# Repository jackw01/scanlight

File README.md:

# A Better Light Source For Scanning Color Negative Film

Left: [scanlight v4](./v4.md), right: [big scanlight](./big.md)

<small>Originally published 2024-08-05, last updated 2026-08-02</small>

## tl;dr

Narrowband trichromatic (RGB) light sources are superior to broadband (white) light for scanning color negative film; there are very good reasons why all commercial film scanners use RGB. ([film scanners were using blue LEDs at least a decade before they would be widely used in consumer products!](https://patents.google.com/patent/JPH09130546A/en?q=(film+scanner+LED)&oq=film+scanner+LED&sort=old)) Scanning film with an RGB light source produces high quality results with minimal post-processing, without the need for specialized software.

### the results

<small>Both scans captured using Fujifilm X-T30. White light scan captured using 95+ CRI 5000K light source. RGB scan captured using custom 450nm+525nm+665nm light source.</small>

## the simplified explanation

Color negative (C-41) film stores an image using cyan, magenta, and yellow dyes. Dyes appear a certain color because they absorb some wavelengths of light; for example, yellow dye mostly absorbs light in the 400-550nm range (which we perceive as violet through green), while allowing other wavelengths (yellow through red) to pass through the film. **These dyes are not intended to produce a human-viewable image, but rather to attenuate certain wavelengths of light for making prints on photosensitive paper.**

White light sources emit light over a broad spectrum of wavelengths. When white light passes through C-41 film, some of these wavelengths are only slightly absorbed by the dyes, which means that these wavelengths aren't useful for recovering the information stored in the individual dye layers - for example, the 580-620nm band (yellow through red-orange light) is mostly transmitted through the film, with a small amount being absorbed by both the magenta and cyan dye layers.

The quality of white light sources is measured with CRI, which represents how well a light source reproduces the true color of a set of standardized color swatches. CRI is effectively a weighted average of how much light a light source emits across different parts of the visible light spectrum, and only a few of these parts matter when it comes to extracting information from color film. **CRI doesn't take into account the deep red (>630nm) and deep blue (<480nm) parts of the spectrum, so as a result, many high-CRI LEDs don't emit much light at these wavelengths, which happen to be where the yellow and cyan dyes absorb the most light.**

<small>note: Standardized scores that take into account these wavelength bands at the edges of the visible spectrum do exist (R9 and R12), but are not readily provided by all LED manufacturers.</small>

With darkroom printing, this is not an issue, as RA-4 color print paper (and motion picture print film) are, by design, most sensitive to specific bands of wavelengths that avoid the crosstalk regions between the dye layers in negative film, and the paper is exposed with an incandescent light source with a smooth emission spectrum across the entire visible range (400-700nm) and beyond.

What about scanning film with a digital camera? Digital camera sensors are designed to capture light in a way that allows for a faithful reproduction of the colors that humans would perceive (this is a gross oversimplification.) C-41 film was *not* designed to be directly viewed by humans.

Not only is the camera sensitive to wavelengths of light that are effectively ignored by RA-4 paper, there is significant crosstalk between the color channel sensitivities of digital camera sensors: light in the ~580-600nm range is seen roughly equally by the red and green channels, and light in the ~480-500nm range is seen by both the green and blue channels.

The red channel of the scan will contain not just information from the red-blocking cyan dye, but also the green-blocking magenta dye. The green channel will contain information from all three dye layers. Additionally, the overall light transmission of C-41 film is heavily biased towards yellow and orange wavelengths due to the orange mask and the relatively large gap between the magenta and cyan dye absorption peaks, which means that **a lot** of light gets through that interferes with both the red and green channels in the camera sensor without carrying much useful information about the colors stored in the film.

<small>note: the orange color of C-41 film is often misunderstood to be the color of the plastic film base, or an orange tint evenly applied over the whole image. It is actually a corrective mask made up of blue- and green-blocking positive images which compensate for deficiencies in the red-sensing and green-sensing layers of the film. For a good explanation of how this works, see [this article](https://observablehq.com/@dorskyee/understanding-color-film). In practice, this means that less-exposed parts of the negative let through disproportionately more yellow, orange, and red light.</small>

So if you scan color negative film with white light, you can't just invert the colors and expect a good result. You need to do some math to try to recover the individual dye layers of the film from ambiguous input data. This can't be done in standard image editing software, which is why dedicated software for negative conversion exists. The level of crosstalk on each channel depends heavily on both the emission spectra of the light source and the spectral sensitivity of the camera, so the conversion process needs to be either calibrated, manually adjusted until it looks “right”, or deduced by the processing software with varying degrees of accuracy. The color depth of the resulting positive image will be relatively low because much of the information recorded by the camera is effectively useless yellow-orange light that has passed through the film without being significantly attenuated by any of the dyes.

To avoid these issues, (almost?) all commercial negative film scanners use a trichromatic narrowband light source with red, green, and blue LEDs to minimize crosstalk between the dye layers in the film and the color channels on the image sensor, and some use monochrome sensors to eliminate sensor crosstalk entirely. When doing it this way, no guesswork is needed to recover a usable image and it's really as simple as inverting the color channels and setting the color balance and black/white points. There is still some crosstalk between camera sensor channels, but now that the light source emits light in three narrow, independently controllable wavelength bands, it can be easily measured and compensated for, or it can be avoided completely by imaging the red, green, and blue channels separately.

### what light source works the best?

When considering the limitations of digital camera sensors, the ideal wavelengths are >650nm for red and <450nm for blue, as shown in the diagram above. Ideally, the green wavelength is 540-560nm to match the absorption peak of the magenta dye, but LEDs in that range are just not practical (see FAQ below for more details), and the standard 525nm works very well.

The next best alternative is to use general purpose RGB LEDs, which typically use 620-630nm for red and 460-480nm for blue. The results will not be the absolute best possible, but will still be far better than with white light. The Fuji Frontier SP3000, a popular professional scanner, uses 630nm for red and 465nm for blue ([source](https://discuss.pixls.us/t/input-color-profile-to-use-for-negatives/20271/13)), but it does not have to contend with the color channel sensitivity of a typical digital camera - it has a monochrome image sensor and combines three exposures taken with red, green, and blue light.

To get the best possible results, I designed my own custom RGB light sources using 665nm red and 455nm blue LEDs. More information on the designs can be found [here (scanlight v4)](./v4.md) and [here (big scanlight)](./big.md). Both light sources allow for individual control of the red, green, and blue channels via a web app. Color balance can be adjusted for single-exposure scanning, and the light can automatically switch colors and trigger a camera to simplify the process of capturing separate exposures for each channel.

All design files for the light sources and film carriers, both current and older versions, can be downloaded from the [GitHub repository](https://github.com/jackw01/scanlight/).

### more sample scans

All scans were processed in [NegPy](https://github.com/marcinz606/NegPy), leaving all settings at the default values. The RGB scans were scanned as **single exposures with all color channels** and sensor crosstalk calibration was applied. The groups of four negatives were scanned and manually processed together in order to demonstrate how the light source affects the overall look of the scans rather than to show a subjectively ideal edit for each photo.

<p align="center"><small>Kodak Ektar 100 (left: white light, right: narrowband RGB light)</small></p>

<p align="center"><small>Fuji 200 (left: white light, right: narrowband RGB light)</small></p>

<p align="center"><small>Kodak Ektar 100 (left: white light, right: narrowband RGB light)</small></p>

<p align="center"><small>Kodak Vision3 500T (left: white light, right: narrowband RGB light)</small></p>

<p align="center"><small>Fuji 200 (left: white light, right: narrowband RGB light)</small></p>

<p align="center"><small>Fuji 200 (left: white light, right: narrowband RGB light)</small></p>

### recommended reading, if you're curious

* Edward J Giorgianni and Thomas E Madden, *Digital Color Management: Encoding Solutions, 2nd Edition*
* Robert L Shanebrook, *Making Kodak Film*

## part 2: responses to frequent questions and comments

<small>Updated 2026-08-02</small>

#### how should i process my scans?
As of 2026, free and open-source film scan processing software exists ([NegPy](https://github.com/marcinz606/NegPy)) which produces excellent results with little effort when inverting single-exposure RGB scans. NegPy uses a processing pipeline which emulates the RA-4 printing process, and supports flat-field correction and automatic merging of trichromatic (separate exposures for red, green, and blue) scans. I would highly recommend this to anyone who is looking to start scanning film at home or is having difficulty with their current processing workflow.

Using software specifically designed for processing white light scans (e.g. Negative Lab Pro) to process RGB scans may give suboptimal results. It's also possible to get good results without using any specialized software, by manually inverting your scans in photo editing software as described below. Manual inversion is much easier with RGB scans than with white light scans, but it still takes more effort than NegPy, and compensating for camera sensor crosstalk may be difficult depending on which image editing software you use.

#### but can't i just edit the white light scan to look like the RGB scan?
You can't get the exact same colors as the RGB scan by adjusting the white balance or individual color channels of a white light scan. This is physically impossible because the light interacted with the film in a fundamentally different way in the white light scan vs. the RGB scan before it was reduced to three bins of wavelengths approximately representing red, green, and blue by the camera sensor; some of the color information stored in the film is lost in this process.

#### but i keep seeing/hearing that using RGB light results in oversaturation or hue shifts
Increasing saturation is often done on purpose to produce a visually striking and not entirely accurate demonstration of why RGB is better (in practice, the differences in color reproduction are more subtle once saturation is equalized), or is the result of processing RGB scans with processing workflows intended to produce normal-looking results with white light scans. No one is saying you can’t adjust saturation in post, or use processing software that produces less-saturated results. Hue shifts are a result of using a processing workflow that doesn't compensate for camera sensor channel crosstalk, and should be a complete non-issue if using the sensor calibration tool in NegPy.

<p align="center"><small>From left to right: RGB scan without sensor calibration (note blue-to-cyan and orange-to-magenta shifts); RGB scan with sensor calibration; Noritsu HS-1800 lab scan</small></p>

#### but the colors in the sample scans still don't look good to me / the colors don't look the way i think film should look
Getting the desired colors from C-41 film, whether by darkroom printing or scanning and editing, has always involved some level of manual adjustment. It is also worth noting that our collective idea of how film is supposed to look is often influenced by highly edited or low-quality scans; old, faded prints; or even software emulations. **Photography is art, and as such it has always involved making subjective decisions about how images should look; all photos are interpretations of raw data and it's up to the photographer to decide what interpretation looks best.** The best starting point for editing is a scan that represents the image data stored in the dye layers of the film with maximum dynamic range and minimal crosstalk.

#### won't this make all film look the same?
Scanning film with RGB light does not neutralize the differences in the "look" of different films; actually, it should produce results that are closer to the intended look of the film when printed on RA-4 paper. The differences in look come from differences in the film's sensitivity to light during exposure and chemical reactions that affect how the dyes are formed during development, not the absorption characteristics of the dyes themselves.

#### should i capture three separate exposures for each color channel?
You can either capture a single image with the red, green, and blue channels on at the same time or capture separate images for each color and merge them later. Both methods can produce satisfactory results. The latter approach has the potential for more technically accurate colors as it eliminates any chance of crosstalk between color channels, but takes significantly more work than capturing a single RGB image which can be processed directly.

When capturing red, green, and blue at the same time, the severity of crosstalk depends heavily on the spectral response of the camera's image sensor and camera manufacturer's color profile, and it may not even be noticeable in many cases. Crosstalk typically manifests as consistent color shifts (usually, reds appearing too pink or greens appearing too yellow,) and can usually be resolved by post-processing with software that supports a crosstalk matrix or RGB primary calibration, such as NegPy (open-source) or Lightroom.

#### how should i adjust the red/green/blue channel levels on the light source?
The red, green, and blue channels on the light source should be adjusted to maximize how much of the camera's dynamic range is utilized on all three color channels. To do this, set the camera white balance to neutral/5000K and adjust the light source so that the histogram peaks on each channel become aligned when the camera is viewing the light through an unexposed, developed piece of film. The deep red (~650nm) and deep blue (~450nm) wavelengths used for RGB scanning are near the edge of what most Bayer-filter image sensors are sensitive to, so some cameras will be significantly more sensitive to one of these wavelengths than others. Therefore, the optimal settings will differ between camera manufacturers and models.

#### should i use narrowband light for scanning color positive (slide) film?
Some people have had success using an adjustable RGB light source for recovering faded slides, but I would not recommend using a narrowband light source for scanning slides that are in good condition. The results I have seen so far are not promising compared to using white light, as colors are typically oversaturated and pink, red, and orange hues become indistinguishable from each other. This likely all comes down to the fact that color positive film is designed to reproduce colors naturally when viewed with a broad-spectrum light source. Any high CRI (95+) white light source should work well. There is some debate over the ideal color temperature: the majority of slide projectors used halogen bulbs with a 3000K-3500K color temperature, but some will argue that a 5000K color temperature should be used instead (this seems to be because Fujifilm datasheets recommend viewing with a ISO 3664 compliant viewer, which historically would have used specialized 5000K high-CRI fluorescent tubes as a light source). I haven't seen a side-by-side comparison, but I would assume that the difference in results would be very subtle or nonexistent if the white balance is corrected when editing the scans.

#### does light source / color matter for scanning black and white film?
No. White and narrowband light sources work equally well for scanning B&W film.

#### what are your thoughts on film carriers?
I have received quite a few emails echoing the sentiment that the film carriers on the market now are generally overpriced for what they are, and there seems to be little correlation between price and user experience. Most film carriers made for DSLR scanning guide the film through a narrow slot with an S-shaped curve on each end to keep it flat. For 35mm film, this seems to generally work well, and based on the reviews and comments I have seen I am not convinced that out of the many film carriers using this design, any perform significantly better than the others. For 120 film, the s-curve design struggles with film flatness when scanning the end frames on cut pieces of film, or if the film is curled across its width. There are a few alternative designs out there that should be able to provide superior film flatness in this case, but I haven't yet seen a thorough quantitative comparison of these. Some of these also involve rough 3D-printed parts coming into direct contact with the film emulsion, which doesn't seem ideal.

##### what about full-border scanning?
Film carriers that allow full-border scanning tend to be significantly worse at keeping the film flat and handling curled film, except for ones that hold the film against glass or acrylic, but those come with other issues (high cost, difficulty keeping the glass clean, Newton's rings, etc.)

#### what lens should i use?
[This list](https://www.pixl-latr.com/how-good-a-macro-lens-do-you-really-need-for-dslr-mirrorless-camera-scanning/) is generally a good starting point. The Micro-Nikkor 55mm f/2.8 AI is my personal recommendation; it outperforms many modern lenses in field flatness, corner-to-corner sharpness, and chromatic aberration, and it is very affordable.

I would **not** recommend low-cost third-party macro lenses like the TTArtisan 40mm f/2.8 Macro or 7artisans 60mm f/2.8 Macro II. While the build quality of these lenses is excellent and they generally have superior contrast to vintage lenses due to better optical coatings, in my experience they cannot match the top tiers of lenses in the above list in corner-to-corner sharpness and lack of chromatic aberration. I would also recommend against using extension tubes with modern lenses; this tends to result in field curvature and other aberrations which can be quite severe depending on the lens.

#### does brightness enhancing film actually work? should i use it?
Brightness enhancing film (BEF) does indeed work to make diffuse light sources more directional, but this can cause other issues. Collimated light makes the image on the film appear slightly sharper, but also exaggerates the appearance of dust and scratches. Depending on the relative positioning of the light source, film, and lens; and type of lens used; grid or moiré patterns may appear due to the structure of the brightness enhancing film and vignetting may occur or become more pronounced. BEF also tends to be difficult to keep clean of dust and fingerprints.

#### what about using an LCD/OLED display as the light source?
OLED displays do contain separate red, green, and blue emitters, but they typically have broader emission spectra than inorganic LEDs, and the red and blue peak wavelengths tend to be closer to 620nm and 470nm respectively. They will produce results with less crosstalk than a white light source, but not as good as RGB LEDs.

Older LCD displays generally emit white light that has been filtered through red, green, and blue filters and recombined. The results will depend on the emission spectrum of the exact display used, and will generally be no better than a white light source. Newer high-gamut LCDs (especially quantum dot LED LCDs) use backlight LEDs with special phosphors designed to emit in narrower bands than typical white LEDs, so they should in theory work as well as OLED.

#### 540-560nm appears to be the ideal green wavelength, why use 525nm?
LEDs in the 540-560nm range are impractical for most uses due to poor efficiency and thus are not widely available. Some GaP green LEDs exist which have peak emission at 555nm, but they are extremely inefficient, requiring hundreds to match the light output of a single 2835 mid-power InGaN LED. Some manufacturers do offer 530-535nm wavelength bins of their InGaN mid-power green LEDs, but these are difficult to source as they are commercially undesirable due to lower efficiency. Applications where a "true green" or "lime green" color is desired usually now use phosphor-converted LEDs, which are very efficient but are suboptimal for film scanning as they output light over a much broader band of wavelengths (60-100nm FWHM vs 15-30nm for direct green LEDs.)

##### how did old film scanners get ~540nm?
They either used cold-cathode fluorescent lamps with phosphors tuned to emit at the desired wavelengths, or used InGaN green LEDs from a higher wavelength bin. These have become increasingly hard to find as manufacturing processes have become more consistent and the industry has settled on ~525nm as the standard green wavelength for lighting and display applications. On the other hand, mid- and high-power ~450nm deep blue and ~660nm deep red LEDs have stayed available alongside their more common ~470nm and ~620nm counterparts due to increased demand, mostly in horticultural applications.

#### why does big scanlight have infrared LEDs?
The IR LEDs are for dust removal – the dyes in color negative film transmit infrared light, but dust does not. By capturing a separate IR image with an IR-sensitive camera, dust particles on the image can be easily located and inpainted. I originally added the LEDs for a specific customer who uses a specialized industrial camera and custom software processing pipeline to do this. As of June 2026, the only free/open-source software I know of that can automate this process is [NegPy](https://github.com/marcinz606/NegPy), although I haven't yet tested it with output from big scanlight.

#### will there be a desktop app for scanlight?
There are no plans for a desktop app right now, since the easiest way to make one by far is to just repackage a web app as a desktop app and there is little to be gained by doing this. It is possible to install the app as a progressive web app on most platforms, which will make it appear as a desktop app and allow it to be used without an internet connection.

#### what if i want to manually invert my scans?
It's definitely much easier to do this with narrowband scans than white light scans, but I still recommend using NegPy due to its automatic analysis and camera sensor calibration abilities.

##### 1. scan
Scan all frames as RAW using fixed white balance and exposure. Exposure should be set such that none of the color channels are clipping.
##### 2. import
Import scans into image editing software. Use a linear RAW profile. Apply lens corrections and use Lens Cast Calibration in Capture One or Flat-Field Correction in Lightroom to compensate for any unevenness in the light source if necessary.
##### 3. d-min balance
Neutralize the color of the minimum density (unexposed) areas of one negative by adjusting the red, green, and blue channel max levels.
##### 4. inversion
Invert the black and white points using the Levels or Curves tool and apply an s-shaped tone curve to adjust contrast. Use the brightness/gamma/Levels tool midpoint controls to adjust the overall scene brightness without affecting the black and white points.
##### 5. fine tuning
Apply the same adjustments to all scans from the same roll of film. Manually fine-tune the black and white points and brightness/gamma for all scans.
##### 6. crosstalk compensation
Use either the primary calibration panel in Lightroom, or the color tools in Capture One (more difficult), correct any hue shifts in the scans. Since hue shifts occur due to crosstalk between camera sensor channels in the light source emission bands, not any property of the film itself, this adjustment should be performed across a broad sample of images and saved for future use.

## license

The PCB schematic, layout, and Gerber files and the 3D CAD files for this project are released under the [CERN Open Hardware Licence Version 2 - Weakly Reciprocal](https://choosealicense.com/licenses/cern-ohl-w-2.0/) (CERN-OHL-W V2). Software and firmware are released under the MIT License. The text and illustrations in this article may not be reproduced without permission.

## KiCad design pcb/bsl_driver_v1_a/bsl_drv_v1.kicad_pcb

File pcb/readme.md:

# PCB revision reference

Revisions of each PCB are listed below in reverse chronological order. Older revisions may have known issues and should not be built - see the errata.md file in each revision's folder.

*Note: big scanlight v1.1 will be released late October-early November 2026.*

| product name                         | part number | revision date | folder            | status                     |
| ------------------------------------ | ----------- | ------------- | ----------------- | -------------------------- |
| **scanlight v4 (rev. b)**            | 26a901b     | 2026-06-28    | sl_v4_b           | **latest (in production)** |
| **big scanlight v1.1 LED array**     | 26b901a     | 2026-10-08    | bsl_array_v1.1_a  | **latest (in production)** |
| **big scanlight v1.1 LED driver**    | 26b902a     | 2026-10-08    | bsl_driver_v1.1_a | **latest (in production)** |
| scanlight v4 (rev. a)                | 26a901a     | 2026-03-29    | sl_v4_a           | discontinued               |
| big scanlight v1 (rev. c) LED array  | 25d901c     | 2026-01-20    | bsl_array_v1_b    | end of life                |
| big scanlight v1 (rev. b) LED driver | 25d902b     | 2026-01-20    | bsl_driver_v1_b   | end of life                |
| big scanlight v1 (rev. b) LED array  | 25d901b     | 2025-11-09    | bsl_array_v1_a    | discontinued               |
| big scanlight v1 (rev. a) LED driver | 25d902a     | 2025-11-09    | bsl_driver_v1_a   | discontinued               |

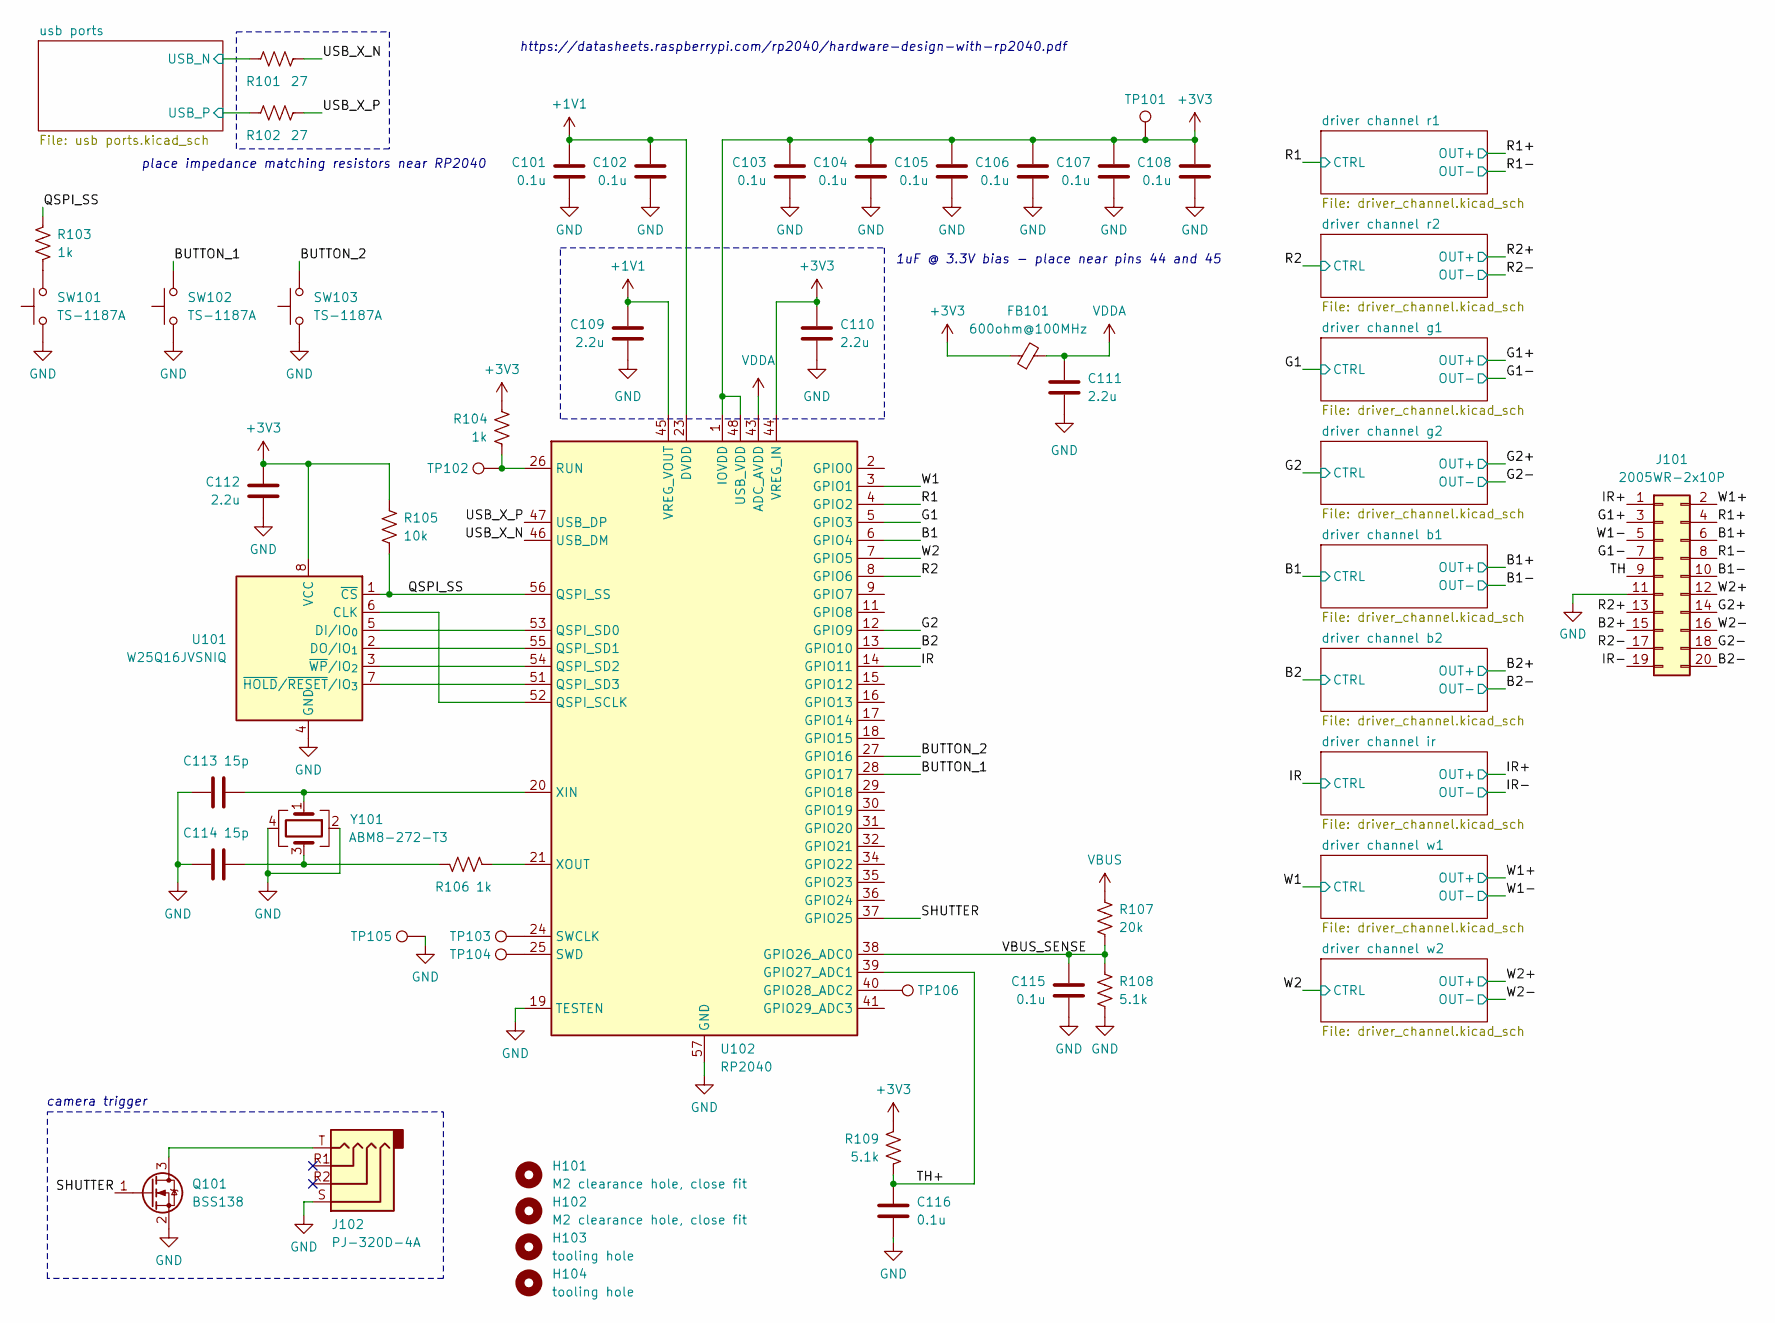
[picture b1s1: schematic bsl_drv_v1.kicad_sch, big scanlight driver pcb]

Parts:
C101, C102, C103, C104, C105, C106, C107, C108, C115, C116: 0.1u; C_0402_1005Metric; MPN CL05B104KB54PNC; LCSC C307331
C109, C110, C111, C112: 2.2u; C_0402_1005Metric; MPN CL05A225MQ5NSNC; LCSC C12530
C113, C114: 15p; C_0402_1005Metric; MPN 0402CG150J500NT; LCSC C1548
FB101: 600ohm@100MHz; L_0603_1608Metric; MPN GZ1608D601TF; LCSC C1002
H101, H102: M2 clearance hole, close fit; MountingHole_2.2mm_M2_Mask_tight
H103, H104: tooling hole; ToolingHole_1.152mm
J101: 2005WR-2x10P; PinHeader_2x10_P2.00mm_Horizontal; MPN 2005WR-2x10P; LCSC C6837626
J102: PJ-320D-4A; Jack_3.5mm_KoreanHropartsElec_PJ-320D-4A_Horizontal; MPN PJ-320D-4A; LCSC C95562
Q101: BSS138; SOT-323_SC-70; MPN BSS138W; LCSC C28646265
R101, R102: 27; R_0402_1005Metric; MPN 0402WGF270JTCE; LCSC C25100
R103, R104, R106: 1k; R_0402_1005Metric; MPN 0402WGF1001TCE; LCSC C11702
R105: 10k; R_0402_1005Metric; MPN 0402WGF1002TCE; LCSC C25744
R107: 20k; R_0402_1005Metric; MPN 0402WGF2002TCE; LCSC C25765
R108, R109: 5.1k; R_0402_1005Metric; MPN 0402WGF5101TCE; LCSC C25905
SW101, SW102, SW103: TS-1187A; SW_PTS526; MPN TS-1187A-B-A-B; LCSC C318884
TP101, TP102, TP103, TP104, TP105, TP106: TestPoint; TestPoint_Pad_D1.0mm
U101: W25Q16JVSNIQ; SOIC-8_3.9x4.9mm_P1.27mm; MPN W25Q16JVSNIQ; LCSC C2456211
U102: RP2040; QFN-56-1EP_7x7mm_P0.4mm_EP3.2x3.2mm; MPN RP2040; LCSC C2040
Y101: ABM8-272-T3; Crystal_SMD_Abracon_ABM8G-4Pin_3.2x2.5mm; MPN ABM8-272-T3; LCSC C20625731

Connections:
+1V1: C101.1, C102.1, C109.1, U102.23 (DVDD), U102.45 (VREG_VOUT), U102.50 (DVDD)
+3V3: C103.1, C104.1, C105.1, C106.1, C107.1, C108.1, C110.1, C112.1, FB101.1, R104.2, R105.1, R109.1, TP101.1, U101.8 (VCC), U102.1 (IOVDD), U102.10 (IOVDD), U102.22 (IOVDD), U102.33 (IOVDD), U102.42 (IOVDD), U102.44 (VREG_IN), U102.48 (USB_VDD), U102.49 (IOVDD); also elsewhere on the board
/B1: U102.6 (GPIO4); also elsewhere on the board
/B1+: J101.6; also elsewhere on the board
/B1-: J101.10; also elsewhere on the board
/B2: U102.13 (GPIO10); also elsewhere on the board
/B2+: J101.15; also elsewhere on the board
/B2-: J101.20; also elsewhere on the board
/BUTTON_1: SW102.2, U102.28 (GPIO17)
/BUTTON_2: SW103.2, U102.27 (GPIO16)
/G1: U102.5 (GPIO3); also elsewhere on the board
/G1+: J101.3; also elsewhere on the board
/G1-: J101.7; also elsewhere on the board
/G2: U102.12 (GPIO9); also elsewhere on the board
/G2+: J101.14; also elsewhere on the board
/G2-: J101.18; also elsewhere on the board
/IR: U102.14 (GPIO11); also elsewhere on the board
/IR+: J101.1; also elsewhere on the board
/IR-: J101.19; also elsewhere on the board
/QSPI_SS: R103.2, R105.2, U101.1 (~CS), U102.56 (QSPI_SS)
/R1: U102.4 (GPIO2); also elsewhere on the board
/R1+: J101.4; also elsewhere on the board
/R1-: J101.8; also elsewhere on the board
/R2: U102.8 (GPIO6); also elsewhere on the board
/R2+: J101.13; also elsewhere on the board
/R2-: J101.17; also elsewhere on the board
/SHUTTER: Q101.1 (G), U102.37 (GPIO25)
/TH: J101.9
/TH+: C116.1, R109.2, U102.39 (GPIO27_ADC1)
/USB_X_N: R101.1, U102.46 (USB_DM)
/USB_X_P: R102.2, U102.47 (USB_DP)
/VBUS_SENSE: C115.1, R107.1, R108.1, U102.38 (GPIO26_ADC0)
/W1: U102.3 (GPIO1); also elsewhere on the board
/W1+: J101.2; also elsewhere on the board
/W1-: J101.5; also elsewhere on the board
/W2: U102.7 (GPIO5); also elsewhere on the board
/W2+: J101.12; also elsewhere on the board
/W2-: J101.16; also elsewhere on the board
/usb ports/USB_N: R101.2; also elsewhere on the board
/usb ports/USB_P: R102.1; also elsewhere on the board
GND: C101.2, C102.2, C103.2, C104.2, C105.2, C106.2, C107.2, C108.2, C109.2, C110.2, C111.2, C112.2, C113.1, C114.1, C115.2, C116.2, J101.11, J102.S, Q101.2 (S), R108.2, SW101.1, SW102.1, SW103.1, TP105.1, U101.4 (GND), U102.19 (TESTEN), U102.57 (GND), Y101.2, Y101.4; also elsewhere on the board
unnamed: C114.2, R106.1, Y101.3
unnamed: J102.T, Q101.3 (D)
unnamed: R103.1, SW101.2
unnamed: U101.6 (CLK), U102.52 (QSPI_SCLK)
unnamed: U101.5 (DI/IO_{0}), U102.53 (QSPI_SD0)
unnamed: U101.2 (DO/IO_{1}), U102.55 (QSPI_SD1)
unnamed: U101.7 (~HOLD/~RESET/IO_{3}), U102.51 (QSPI_SD3)
unnamed: U101.3 (~WP/IO_{2}), U102.54 (QSPI_SD2)
unnamed: TP106.1, U102.40 (GPIO28_ADC2)
unnamed: R104.1, TP102.1, U102.26 (RUN)
unnamed: TP103.1, U102.24 (SWCLK)
unnamed: TP104.1, U102.25 (SWD)
unnamed: C113.2, U102.20 (XIN), Y101.1
unnamed: R106.2, U102.21 (XOUT)
VBUS: R107.2; also elsewhere on the board
VDDA: C111.1, FB101.2, U102.43 (ADC_AVDD)

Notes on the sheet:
place impedance matching resistors near RP2040
1uF @ 3.3V bias - place near pins 44 and 45
camera trigger
https://datasheets.raspberrypi.com/rp2040/hardware-design-with-rp2040.pdf

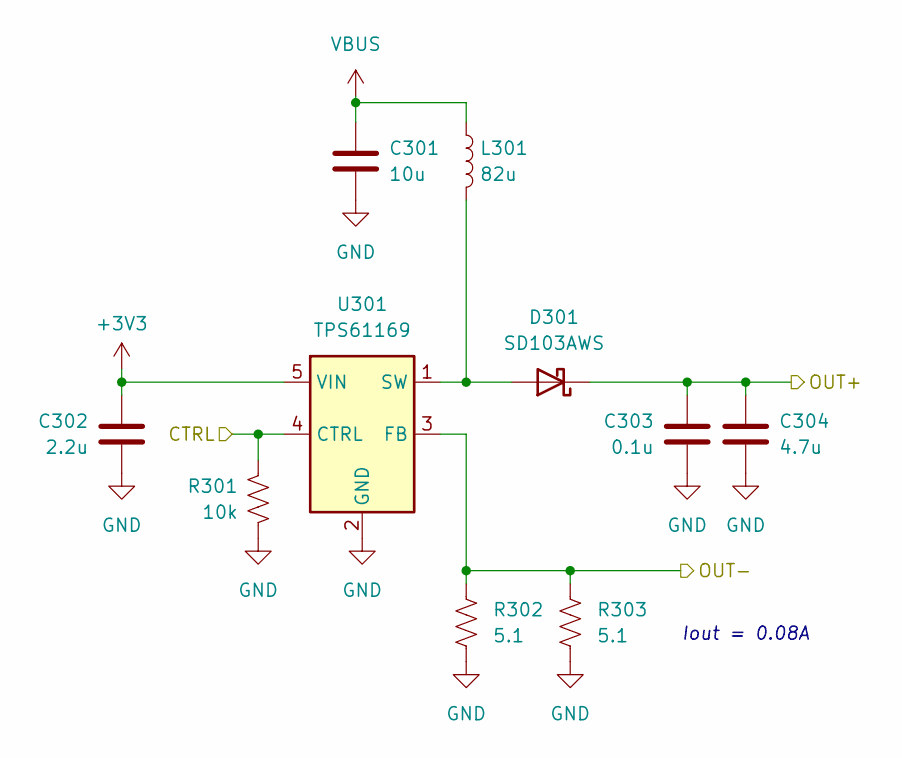
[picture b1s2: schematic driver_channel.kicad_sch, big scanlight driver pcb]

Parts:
C301: 10u; C_0805_2012Metric; MPN CL21A106KAYNNNE; LCSC C15850
C302: 2.2u; C_0402_1005Metric; MPN CL05A225MQ5NSNC; LCSC C12530
C303: 0.1u; C_0402_1005Metric; MPN CL05B104KB54PNC; LCSC C307331
C304: 4.7u; C_1206_3216Metric; MPN 1206B475K500NT; LCSC C29823
D301: SD103AWS; D_SOD-323; MPN SD103AWS; LCSC C7420360
L301: 82u; L_Sunlord_SWPA6028S; MPN CR6028-820M; LCSC C7588760
R301: 10k; R_0402_1005Metric; MPN 0402WGF1002TCE; LCSC C25744
R302, R303: 5.1; R_0603_1608Metric; MPN 0603WAF510KT5E; LCSC C25197
U301: TPS61169; SOT-353_SC-70-5; MPN TPS61169DCKR; LCSC C71045

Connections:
+3V3: C302.1, U301.5 (VIN); also elsewhere on the board
/R1: R301.1, U301.4 (CTRL); also elsewhere on the board
/R1+: C303.1, C304.1, D301.1 (K); also elsewhere on the board
/R1-: R302.1, R303.1, U301.3 (FB); also elsewhere on the board
GND: C301.2, C302.2, C303.2, C304.2, R301.2, R302.2, R303.2, U301.2 (GND); also elsewhere on the board
unnamed: D301.2 (A), L301.2, U301.1 (SW)
VBUS: C301.1, L301.1; also elsewhere on the board

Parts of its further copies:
C401, C501, C601, C701, C801, C901, C1001, C1101: 10u; C_0805_2012Metric; MPN CL21A106KAYNNNE; LCSC C15850
C402, C502, C602, C702, C802, C902, C1002, C1102: 2.2u; C_0402_1005Metric; MPN CL05A225MQ5NSNC; LCSC C12530
C403, C503, C603, C703, C803, C903, C1003, C1103: 0.1u; C_0402_1005Metric; MPN CL05B104KB54PNC; LCSC C307331
C404, C504, C604, C704, C804, C904, C1004, C1104: 4.7u; C_1206_3216Metric; MPN 1206B475K500NT; LCSC C29823
D401, D501, D601, D701, D801, D901, D1001, D1101: SD103AWS; D_SOD-323; MPN SD103AWS; LCSC C7420360
L401, L501, L601, L701, L801, L901, L1001, L1101: 82u; L_Sunlord_SWPA6028S; MPN CR6028-820M; LCSC C7588760
R401, R501, R601, R701, R801, R901, R1001, R1101: 10k; R_0402_1005Metric; MPN 0402WGF1002TCE; LCSC C25744
R402, R403, R502, R503, R602, R603, R702, R703, R802, R803, R902, R903, R1002, R1003, R1102, R1103: 5.1; R_0603_1608Metric; MPN 0603WAF510KT5E; LCSC C25197
U401, U501, U601, U701, U801, U901, U1001, U1101: TPS61169; SOT-353_SC-70-5; MPN TPS61169DCKR; LCSC C71045

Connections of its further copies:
+3V3: C402.1, C502.1, C602.1, C702.1, C802.1, C902.1, C1002.1, C1102.1, U401.5 (VIN), U501.5 (VIN), U601.5 (VIN), U701.5 (VIN), U801.5 (VIN), U901.5 (VIN), U1001.5 (VIN), U1101.5 (VIN); also elsewhere on the board
/B1: R701.1, U701.4 (CTRL); also elsewhere on the board
/B1+: C703.1, C704.1, D701.1 (K); also elsewhere on the board
/B1-: R702.1, R703.1, U701.3 (FB); also elsewhere on the board
/B2: R801.1, U801.4 (CTRL); also elsewhere on the board
/B2+: C803.1, C804.1, D801.1 (K); also elsewhere on the board
/B2-: R802.1, R803.1, U801.3 (FB); also elsewhere on the board
/G1: R501.1, U501.4 (CTRL); also elsewhere on the board
/G1+: C503.1, C504.1, D501.1 (K); also elsewhere on the board
/G1-: R502.1, R503.1, U501.3 (FB); also elsewhere on the board
/G2: R601.1, U601.4 (CTRL); also elsewhere on the board
/G2+: C603.1, C604.1, D601.1 (K); also elsewhere on the board
/G2-: R602.1, R603.1, U601.3 (FB); also elsewhere on the board
/IR: R901.1, U901.4 (CTRL); also elsewhere on the board
/IR+: C903.1, C904.1, D901.1 (K); also elsewhere on the board
/IR-: R902.1, R903.1, U901.3 (FB); also elsewhere on the board
/R2: R401.1, U401.4 (CTRL); also elsewhere on the board
/R2+: C403.1, C404.1, D401.1 (K); also elsewhere on the board
/R2-: R402.1, R403.1, U401.3 (FB); also elsewhere on the board
/W1: R1001.1, U1001.4 (CTRL); also elsewhere on the board
/W1+: C1003.1, C1004.1, D1001.1 (K); also elsewhere on the board
/W1-: R1002.1, R1003.1, U1001.3 (FB); also elsewhere on the board
/W2: R1101.1, U1101.4 (CTRL); also elsewhere on the board
/W2+: C1103.1, C1104.1, D1101.1 (K); also elsewhere on the board
/W2-: R1102.1, R1103.1, U1101.3 (FB); also elsewhere on the board
GND: C401.2, C402.2, C403.2, C404.2, C501.2, C502.2, C503.2, C504.2, C601.2, C602.2, C603.2, C604.2, C701.2, C702.2, C703.2, C704.2, C801.2, C802.2, C803.2, C804.2, C901.2, C902.2, C903.2, C904.2, C1001.2, C1002.2, C1003.2, C1004.2, C1101.2, C1102.2, C1103.2, C1104.2, R401.2, R402.2, R403.2, R501.2, R502.2, R503.2, R601.2, R602.2, R603.2, R701.2, R702.2, R703.2, R801.2, R802.2, R803.2, R901.2, R902.2, R903.2, R1001.2, R1002.2, R1003.2, R1101.2, R1102.2, R1103.2, U401.2 (GND), U501.2 (GND), U601.2 (GND), U701.2 (GND), U801.2 (GND), U901.2 (GND), U1001.2 (GND), U1101.2 (GND); also elsewhere on the board
unnamed: D401.2 (A), L401.2, U401.1 (SW)
unnamed: D501.2 (A), L501.2, U501.1 (SW)
unnamed: D601.2 (A), L601.2, U601.1 (SW)
unnamed: D701.2 (A), L701.2, U701.1 (SW)
unnamed: D801.2 (A), L801.2, U801.1 (SW)
unnamed: D901.2 (A), L901.2, U901.1 (SW)
unnamed: D1001.2 (A), L1001.2, U1001.1 (SW)
unnamed: D1101.2 (A), L1101.2, U1101.1 (SW)
VBUS: C401.1, C501.1, C601.1, C701.1, C801.1, C901.1, C1001.1, C1101.1, L401.1, L501.1, L601.1, L701.1, L801.1, L901.1, L1001.1, L1101.1; also elsewhere on the board

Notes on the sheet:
Iout = 0.08A

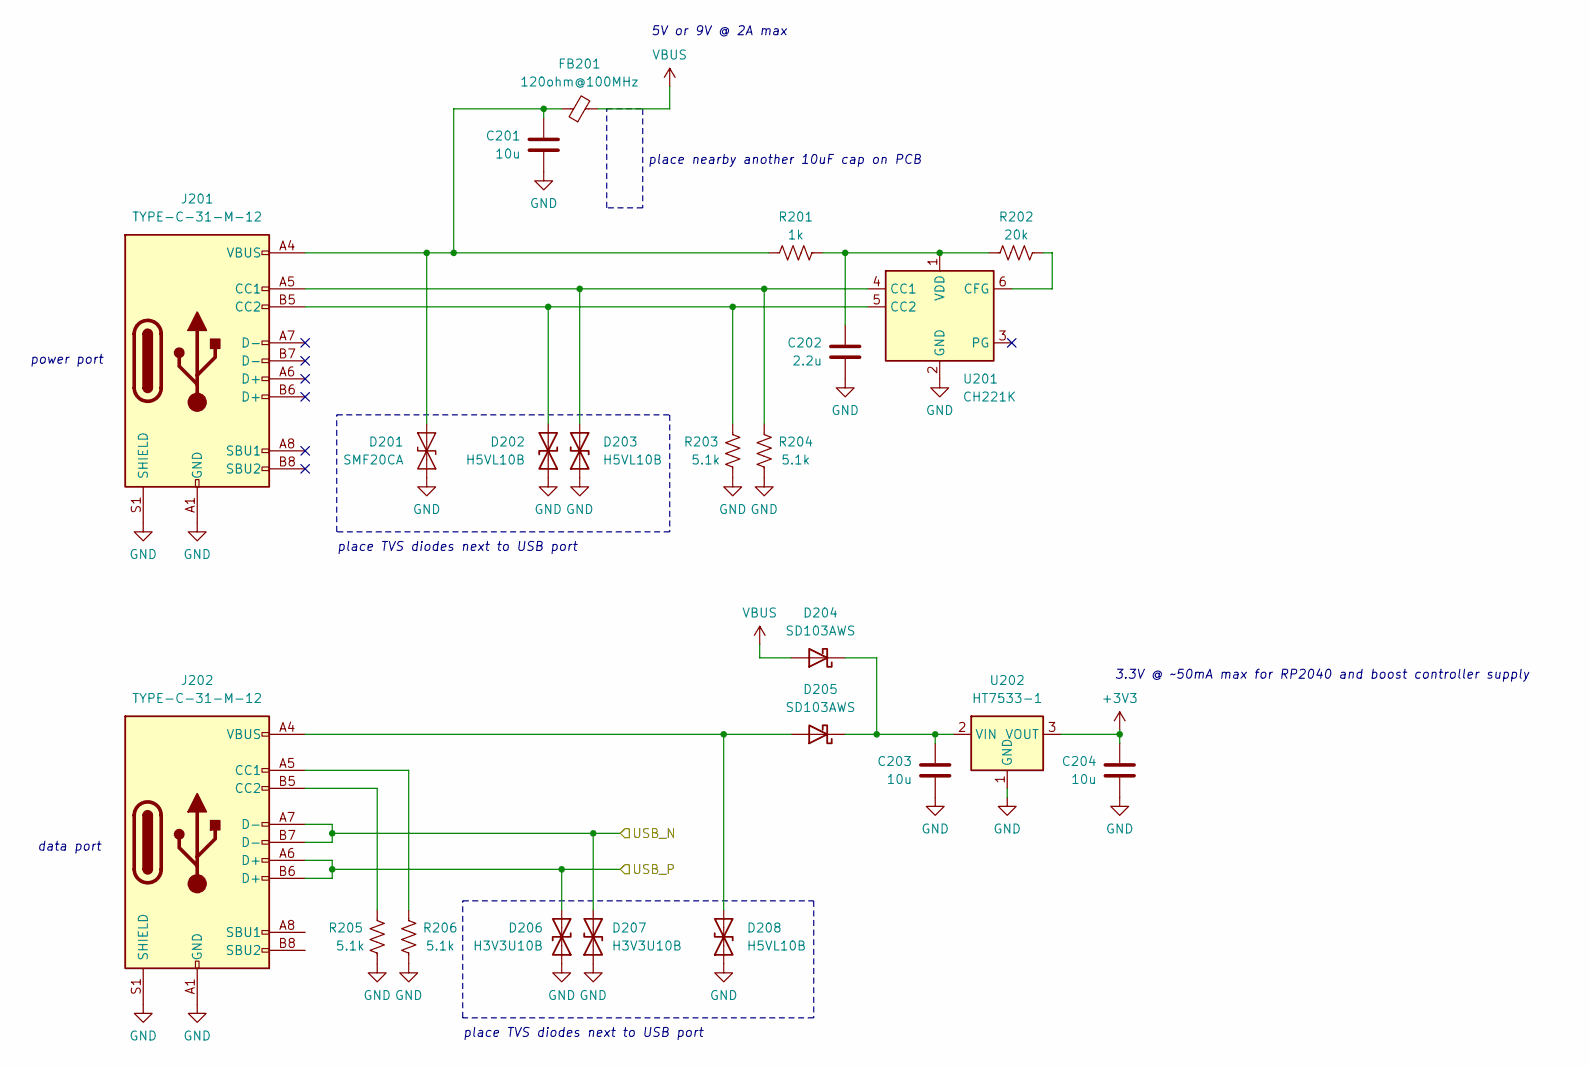
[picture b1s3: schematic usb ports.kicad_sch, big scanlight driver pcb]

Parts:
C201, C203, C204: 10u; C_0805_2012Metric; MPN CL21A106KAYNNNE; LCSC C15850
C202: 2.2u; C_0402_1005Metric; MPN CL05A225MQ5NSNC; LCSC C12530
D201: SMF20CA; D_SOD-123F; MPN SMF20CA; LCSC C42371747
D202, D203, D208: H5VL10B; D_SOD-882; MPN H5VL10B; LCSC C7420372
D204, D205: SD103AWS; D_SOD-323; MPN SD103AWS; LCSC C7420360
D206, D207: H3V3U10B; D_SOD-882; MPN H3V3U10B; LCSC C20615782
FB201: 120ohm@100MHz; L_0805_2012Metric; MPN UPZ2012E121-4R0TF; LCSC C97001
J201, J202: TYPE-C-31-M-12; USB_C_Receptacle_HRO_TYPE-C-31-M-12; MPN TYPE-C-31-M-12; LCSC C165948
R201: 1k; R_0402_1005Metric; MPN 0402WGF1001TCE; LCSC C11702
R202: 20k; R_0402_1005Metric; MPN 0402WGF2002TCE; LCSC C25765
R203, R204, R205, R206: 5.1k; R_0402_1005Metric; MPN 0402WGF5101TCE; LCSC C25905
U201: CH221K; SOT-23-6; MPN CH221K; LCSC C5125736
U202: HT7533-1; SOT-89-3; MPN HT7533-1; LCSC C14289

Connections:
+3V3: C204.1, U202.3 (VOUT); also elsewhere on the board
/usb ports/USB_N: D207.2 (A2), J202.A7 (D-), J202.B7 (D-); also elsewhere on the board
/usb ports/USB_P: D206.2 (A2), J202.A6 (D+), J202.B6 (D+); also elsewhere on the board
GND: C201.2, C202.2, C203.2, C204.2, D201.1 (A1), D202.1 (A1), D203.1 (A1), D206.1 (A1), D207.1 (A1), D208.1 (A1), J201.A1 (GND), J201.A12 (GND), J201.B1 (GND), J201.B12 (GND), J201.S1 (SHIELD), J202.A1 (GND), J202.A12 (GND), J202.B1 (GND), J202.B12 (GND), J202.S1 (SHIELD), R203.1, R204.2, R205.1, R206.2, U201.2 (GND), U202.1 (GND); also elsewhere on the board
unnamed: C201.1, D201.2 (A2), FB201.1, J201.A4 (VBUS), J201.A9 (VBUS), J201.B4 (VBUS), J201.B9 (VBUS), R201.2
unnamed: D202.2 (A2), J201.B5 (CC2), R203.2, U201.5 (CC2)
unnamed: D203.2 (A2), J201.A5 (CC1), R204.1, U201.4 (CC1)
unnamed: C203.1, D204.1 (K), D205.1 (K), U202.2 (VIN)
unnamed: D205.2 (A), D208.2 (A2), J202.A4 (VBUS), J202.A9 (VBUS), J202.B4 (VBUS), J202.B9 (VBUS)
unnamed: J202.A5 (CC1), R206.1
unnamed: J202.B5 (CC2), R205.2
unnamed: R202.1, U201.6 (CFG)
unnamed: C202.1, R201.1, R202.2, U201.1 (VDD)
VBUS: D204.2 (A), FB201.2; also elsewhere on the board

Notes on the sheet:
place TVS diodes next to USB port
power port
place nearby another 10uF cap on PCB
5V or 9V @ 2A max
3.3V @ ~50mA max for RP2040 and boost controller supply
data port

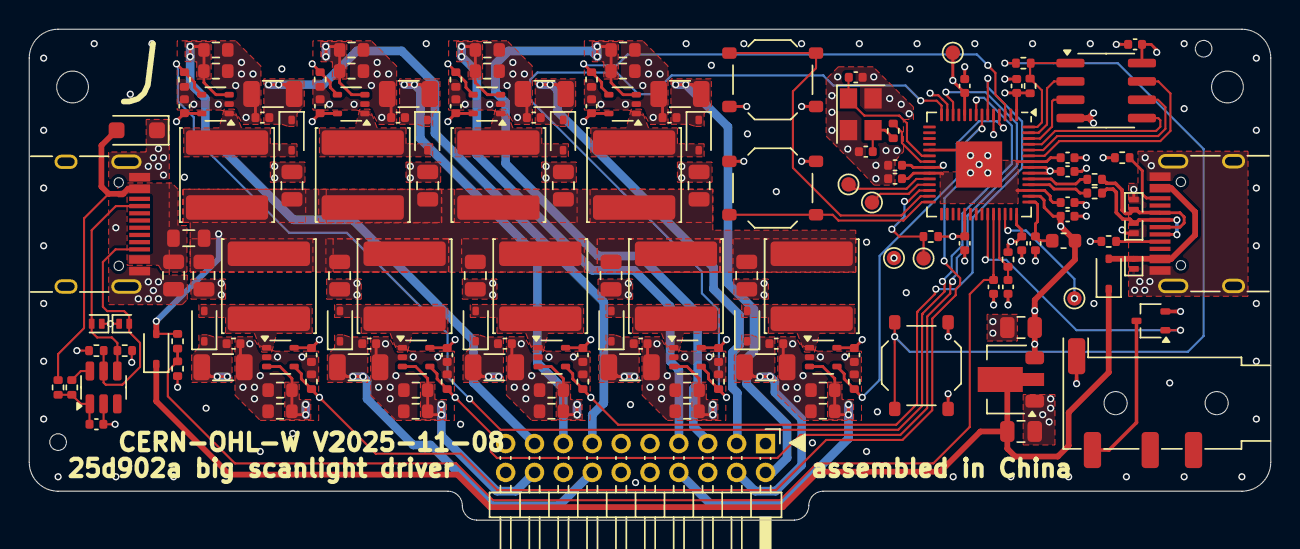
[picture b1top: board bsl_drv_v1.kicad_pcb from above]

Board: 4 copper layers, 86.0 x 34.0 mm, 158 parts (0 on the bottom side), 74 nets.

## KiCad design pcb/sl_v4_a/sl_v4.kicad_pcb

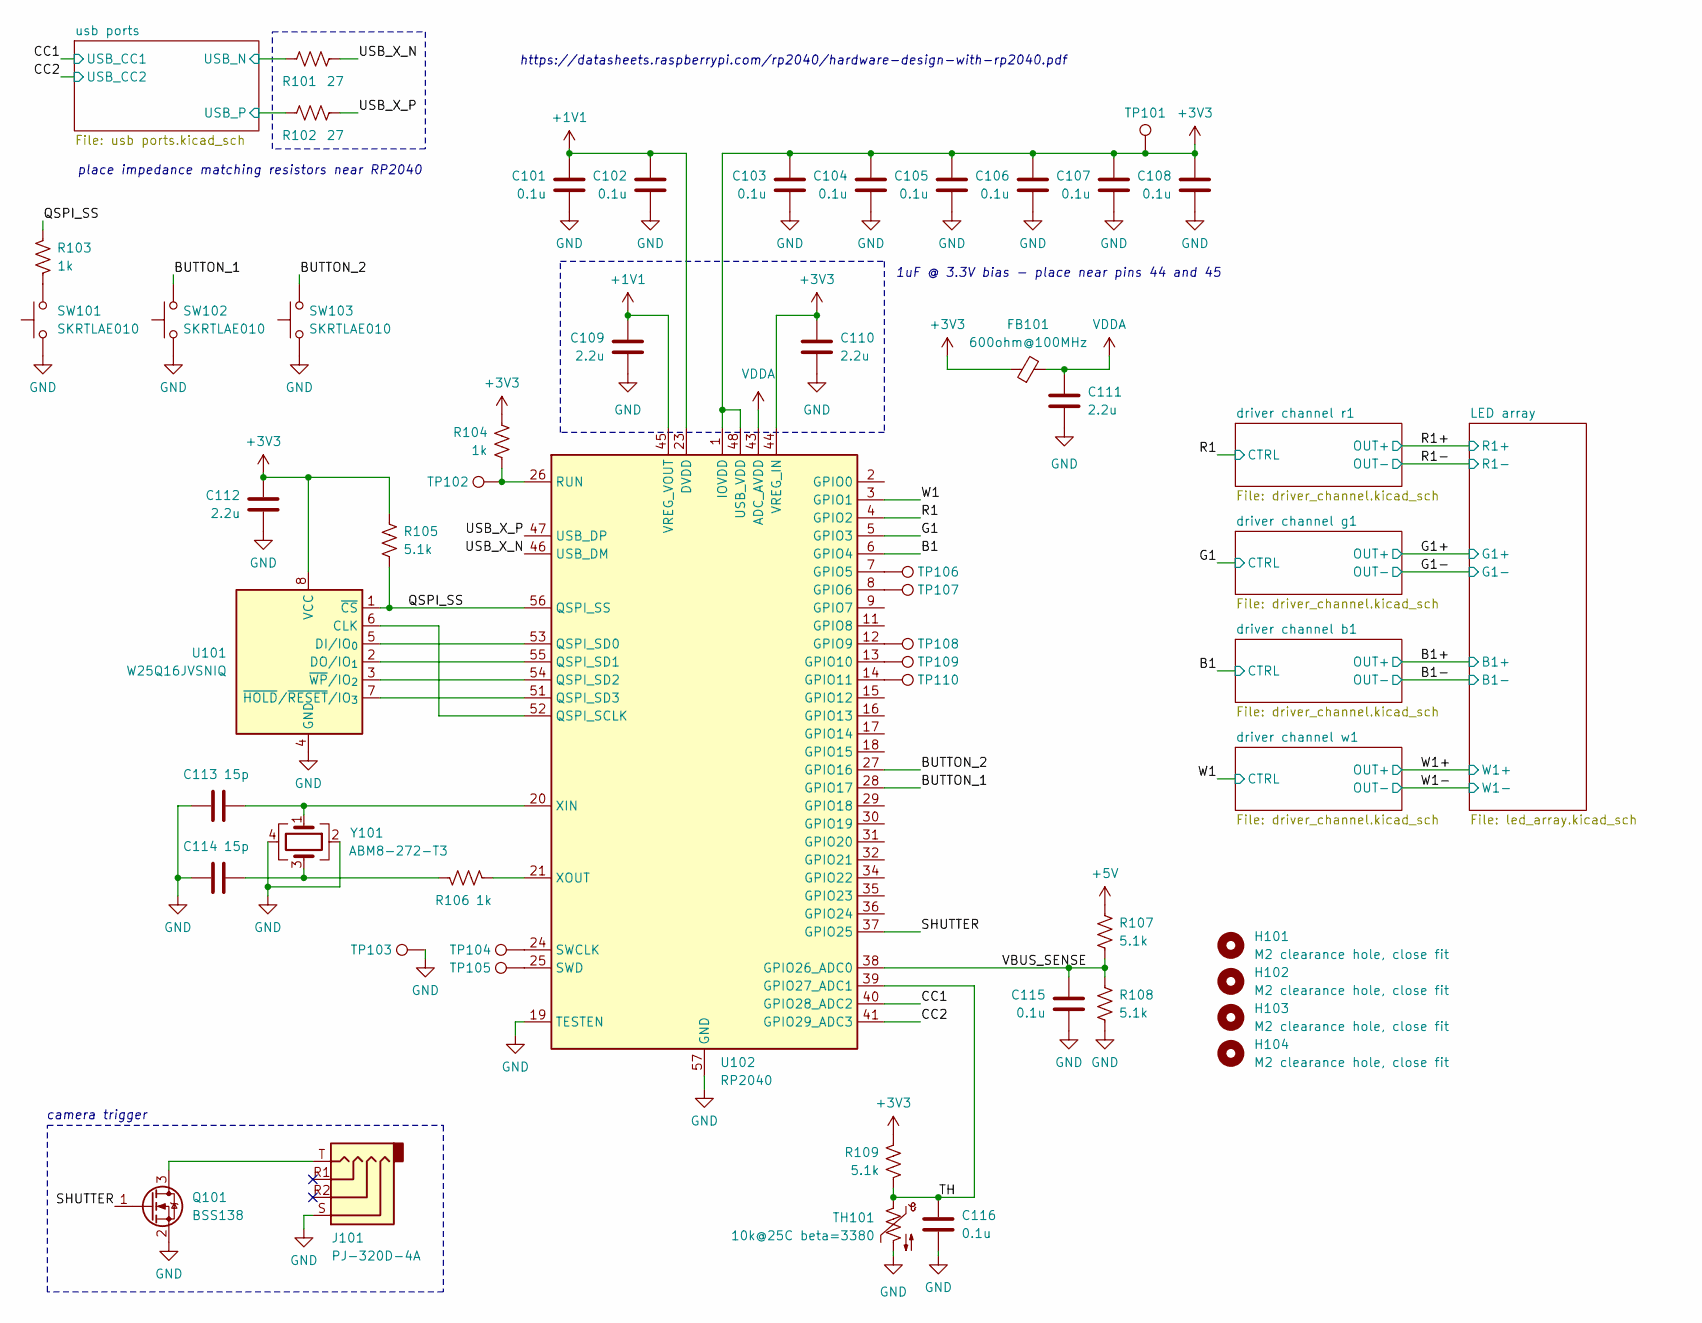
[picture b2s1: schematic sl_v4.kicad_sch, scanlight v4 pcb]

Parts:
C101, C102, C103, C104, C105, C106, C107, C108, C115, C116: 0.1u; C_0402_1005Metric; MPN CL05B104KB54PNC; LCSC C307331
C109, C110, C111, C112: 2.2u; C_0402_1005Metric; MPN CL05A225MQ5NSNC; LCSC C12530
C113, C114: 15p; C_0402_1005Metric; MPN 0402CG150J500NT; LCSC C1548
FB101: 600ohm@100MHz; L_0603_1608Metric; MPN GZ1608D601TF; LCSC C1002
H101, H102, H103, H104: M2 clearance hole, close fit; MountingHole_2.2mm_M2_Mask_tight
J101: PJ-320D-4A; Jack_3.5mm_KoreanHropartsElec_PJ-320D-4A_Horizontal; MPN PJ-320D-4A; LCSC C95562
Q101: BSS138; SOT-323_SC-70; MPN BSS138W; LCSC C28646265
R101, R102: 27; R_0402_1005Metric; MPN 0402WGF270JTCE; LCSC C25100
R103, R104, R106: 1k; R_0402_1005Metric; MPN 0402WGF1001TCE; LCSC C11702
R105, R107, R108, R109: 5.1k; R_0402_1005Metric; MPN 0402WGF5101TCE; LCSC C25905
SW101, SW102, SW103: SKRTLAE010; SW_Push_1P1T-MP_NO_Horizontal_Alps_SKRTLAE010; MPN SKRTLAE010; LCSC C110293
TH101: 10k@25C beta=3380; R_0603_1608Metric; MPN NCP18XH103F03RB; LCSC C13564
TP101, TP102, TP103, TP104, TP105, TP106, TP107, TP108, TP109, TP110: TestPoint; TestPoint_Pad_D1.0mm
U101: W25Q16JVSNIQ; SOIC-8_3.9x4.9mm_P1.27mm; MPN W25Q16JVSNIQ; LCSC C2456211
U102: RP2040; QFN-56-1EP_7x7mm_P0.4mm_EP3.2x3.2mm; MPN RP2040; LCSC C2040
Y101: ABM8-272-T3; Crystal_SMD_Abracon_ABM8G-4Pin_3.2x2.5mm; MPN ABM8-272-T3; LCSC C20625731

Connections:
+1V1: C101.1, C102.1, C109.1, U102.23 (DVDD), U102.45 (VREG_VOUT), U102.50 (DVDD)
+3V3: C103.1, C104.1, C105.1, C106.1, C107.1, C108.1, C110.1, C112.1, FB101.1, R104.2, R105.1, R109.1, TP101.1 (1_1), U101.8 (VCC), U102.1 (IOVDD), U102.10 (IOVDD), U102.22 (IOVDD), U102.33 (IOVDD), U102.42 (IOVDD), U102.44 (VREG_IN), U102.48 (USB_VDD), U102.49 (IOVDD); also elsewhere on the board
+5V: R107.2; also elsewhere on the board
/B1: U102.6 (GPIO4); also elsewhere on the board
/BUTTON_1: SW102.2, U102.28 (GPIO17)
/BUTTON_2: SW103.2, U102.27 (GPIO16)
/CC1: U102.40 (GPIO28_ADC2); also elsewhere on the board
/CC2: U102.41 (GPIO29_ADC3); also elsewhere on the board
/G1: U102.5 (GPIO3); also elsewhere on the board
/QSPI_SS: R103.2, R105.2, U101.1 (~CS), U102.56 (QSPI_SS)
/R1: U102.4 (GPIO2); also elsewhere on the board
/SHUTTER: Q101.1 (G), U102.37 (GPIO25)
/TH: C116.1, R109.2, TH101.1, U102.39 (GPIO27_ADC1)
/USB_X_N: R101.1, U102.46 (USB_DM)
/USB_X_P: R102.2, U102.47 (USB_DP)
/VBUS_SENSE: C115.1, R107.1, R108.1, U102.38 (GPIO26_ADC0)
/W1: U102.3 (GPIO1); also elsewhere on the board
/usb ports/USB_N: R101.2; also elsewhere on the board
/usb ports/USB_P: R102.1; also elsewhere on the board
GND: C101.2, C102.2, C103.2, C104.2, C105.2, C106.2, C107.2, C108.2, C109.2, C110.2, C111.2, C112.2, C113.1, C114.1, C115.2, C116.2, J101.S, Q101.2 (S), R108.2, SW101.1, SW102.1, SW103.1, TH101.2, TP103.1 (1_1), U101.4 (GND), U102.19 (TESTEN), U102.57 (GND), Y101.2, Y101.4; also elsewhere on the board
unnamed: C114.2, R106.1, Y101.3
unnamed: J101.T, Q101.3 (D)
unnamed: R103.1, SW101.2
unnamed: U101.6 (CLK), U102.52 (QSPI_SCLK)
unnamed: U101.5 (DI/IO_{0}), U102.53 (QSPI_SD0)
unnamed: U101.2 (DO/IO_{1}), U102.55 (QSPI_SD1)
unnamed: U101.7 (~HOLD/~RESET/IO_{3}), U102.51 (QSPI_SD3)
unnamed: U101.3 (~WP/IO_{2}), U102.54 (QSPI_SD2)
unnamed: TP106.1 (1_1), U102.7 (GPIO5)
unnamed: TP107.1 (1_1), U102.8 (GPIO6)
unnamed: TP108.1 (1_1), U102.12 (GPIO9)
unnamed: TP109.1 (1_1), U102.13 (GPIO10)
unnamed: TP110.1 (1_1), U102.14 (GPIO11)
unnamed: R104.1, TP102.1 (1_1), U102.26 (RUN)
unnamed: TP104.1 (1_1), U102.24 (SWCLK)
unnamed: TP105.1 (1_1), U102.25 (SWD)
unnamed: C113.2, U102.20 (XIN), Y101.1
unnamed: R106.2, U102.21 (XOUT)
VDDA: C111.1, FB101.2, U102.43 (ADC_AVDD)

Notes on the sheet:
place impedance matching resistors near RP2040
1uF @ 3.3V bias - place near pins 44 and 45
camera trigger
https://datasheets.raspberrypi.com/rp2040/hardware-design-with-rp2040.pdf

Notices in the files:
pcb/bsl_array_v1.1/bsl_array_v1.kicad_pcb:
25d901c big scanlight array PCB  2026-01-19  CERN-OHL-W V2  RoHS compliant  made in China
pcb/sl_v4_a/sl_v4.kicad_pcb:
made in China  RoHS compliant  CERN-OHL-W V2
